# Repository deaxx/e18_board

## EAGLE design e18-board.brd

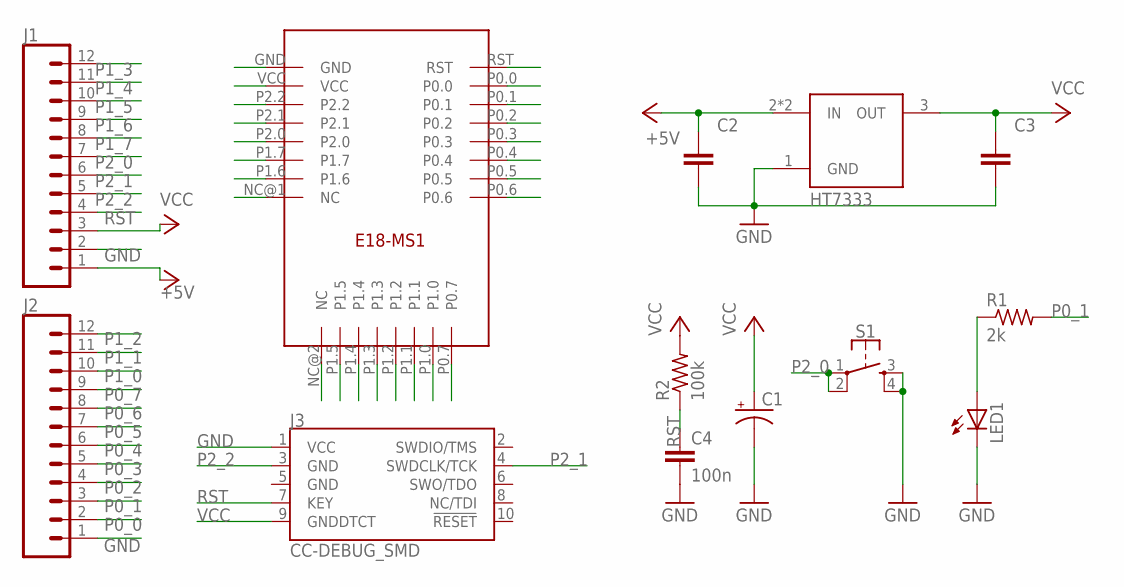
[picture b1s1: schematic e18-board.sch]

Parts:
C1: 100uF; EIA7343
C2, C3: C_TANTALUM-1411(3528-METRIC); CAPM3528X210
C4: 100n; 0603
J1, J2: CONN_12NO_SILK; 1X12_NO_SILK
J3: CC-DEBUG_SMD; SAMTECH_FTSH-105-01
LED1: LEDCHIPLED_0805; CHIPLED_0805
R1: 2k; R0603
R2: 100k; R0603
S1: MOMENTARY-SWITCH-SPST-2-SMD-5.2MM; TACTILE_SWITCH_SMD_5.2MM
U$1: E18-MS1PCB; E18-MS1-PCB
U$2: HT7333; SOT89

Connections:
+5V: C2.1, J1.1, U$2.2 (IN), U$2.2@1 (IN)
GND: C1.C (-), C2.2, C3.2, C4.2, J1.2, J2.1, J3.1 (VCC), LED1.C, S1.3, S1.4, U$1.GND, U$2.1 (GND)
unnamed: LED1.A, R1.1
P0_0: J2.2, U$1.P0.0
P0_1: J2.3, R1.2, U$1.P0.1
P0_2: J2.4, U$1.P0.2
P0_3: J2.5, U$1.P0.3
P0_4: J2.6, U$1.P0.4
P0_5: J2.7, U$1.P0.5
P0_6: J2.8, U$1.P0.6
P0_7: J2.9, U$1.P0.7
P1_0: J2.10, U$1.P1.0
P1_1: J2.11, U$1.P1.1
P1_2: J2.12, U$1.P1.2
P1_3: J1.12, U$1.P1.3
P1_4: J1.11, U$1.P1.4
P1_5: J1.10, U$1.P1.5
P1_6: J1.9, U$1.P1.6
P1_7: J1.8, U$1.P1.7
P2_0: J1.7, S1.1, S1.2, U$1.P2.0
P2_1: J1.6, J3.4 (SWDCLK/TCK), U$1.P2.1
P2_2: J1.5, J3.3 (GND), U$1.P2.2
RST: C4.1, J1.4, J3.7 (KEY), R2.1, U$1.RST
VCC: C1.A (+), C3.1, J1.3, J3.9 (GNDDTCT), R2.2, U$1.VCC, U$2.3 (OUT)

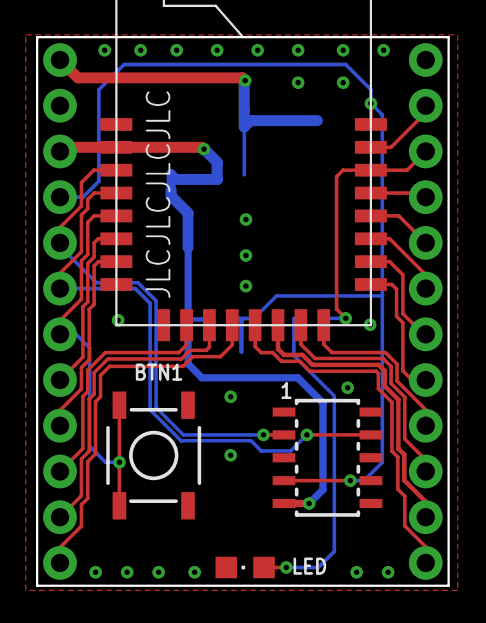
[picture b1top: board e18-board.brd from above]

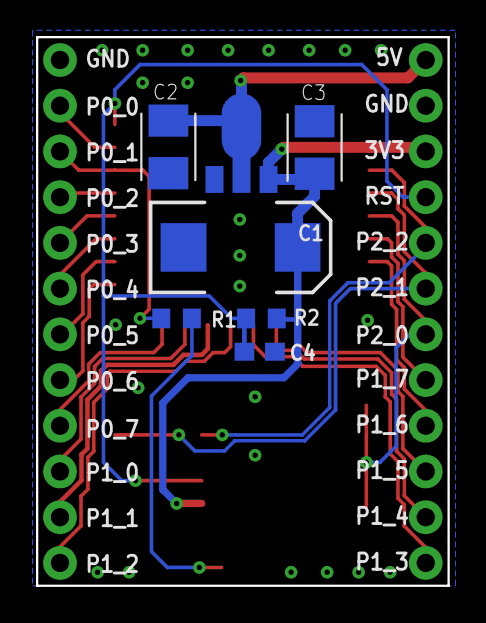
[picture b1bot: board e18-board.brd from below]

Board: 2 copper layers, 22.9 x 30.5 mm, 13 parts (7 on the bottom side), 24 nets.

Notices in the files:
parts and their libraries:
SparkFun-Connectors: Licensing: Creative Commons ShareAlike 4.0 International - https://creativecommons.org/licenses/by-sa/4.0
